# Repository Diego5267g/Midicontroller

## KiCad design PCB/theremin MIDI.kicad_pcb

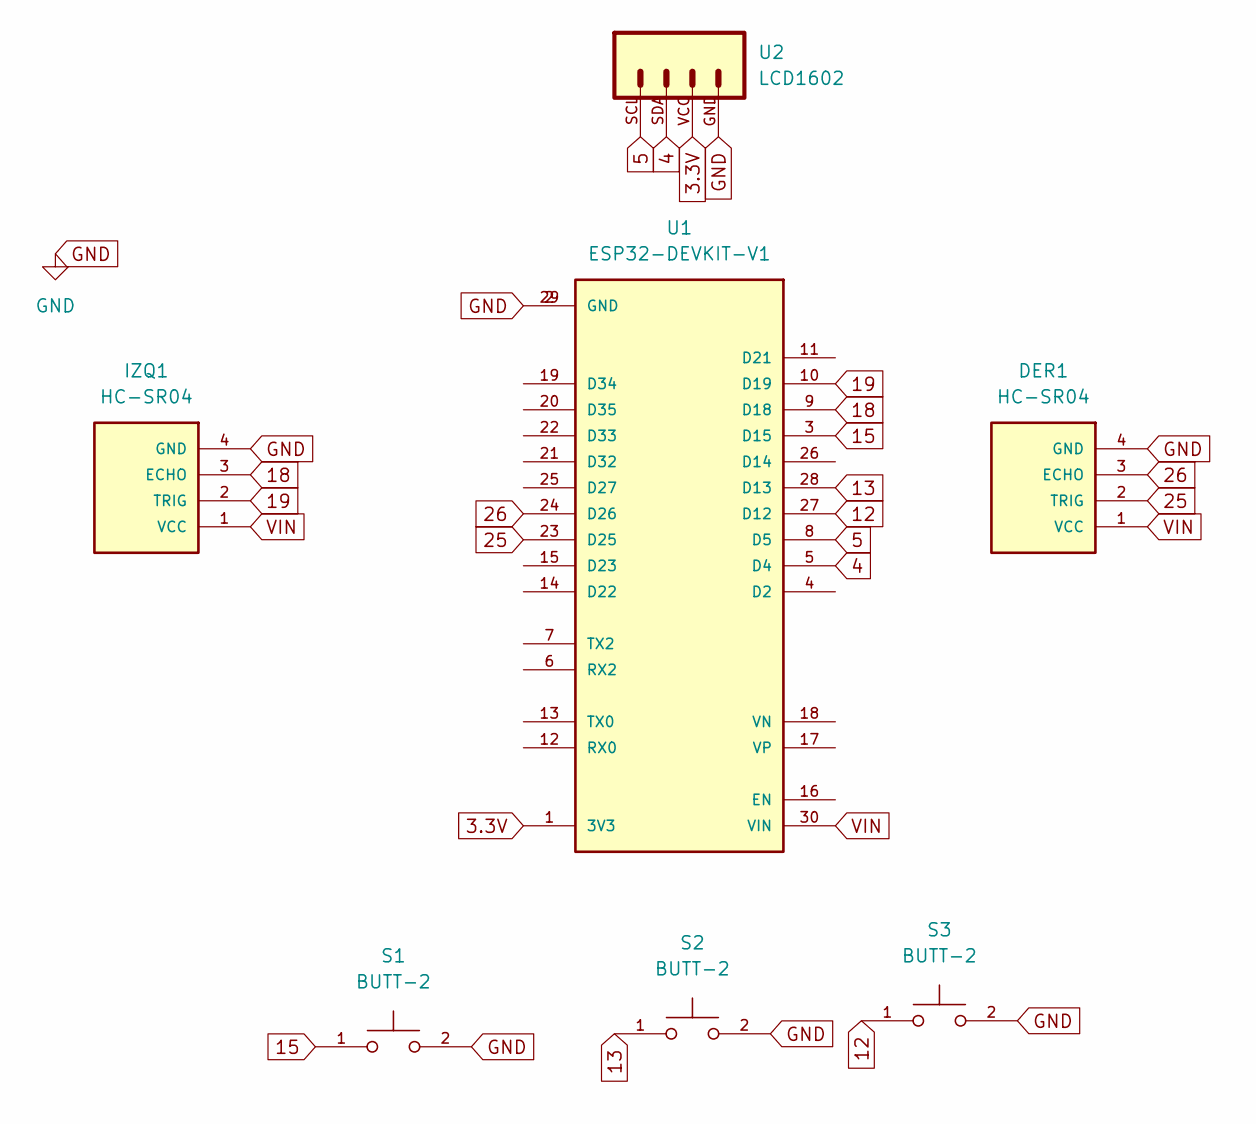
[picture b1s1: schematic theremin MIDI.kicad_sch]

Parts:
DER1: HC-SR04; XCVR_HC-SR04
IZQ1: HC-SR04; XCVR_HC-SR04
S1, S2, S3: BUTT-2; SW_BUTT-2; PARTREV N/A
U1: ESP32-DEVKIT-V1; MODULE_ESP32_DEVKIT_V1; PARTREV N/A
U2: LCD1602; LCD1602-PORT

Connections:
3.3V: U1.1 (3V3), U2.VCC
4: U1.5 (D4), U2.SDA
5: U1.8 (D5), U2.SCL
12: S3.1, U1.27 (D12)
13: S2.1, U1.28 (D13)
15: S1.1, U1.3 (D15)
18: IZQ1.3 (ECHO), U1.9 (D18)
19: IZQ1.2 (TRIG), U1.10 (D19)
25: DER1.2 (TRIG), U1.23 (D25)
26: DER1.3 (ECHO), U1.24 (D26)
GND: DER1.4 (GND), IZQ1.4 (GND), S1.2, S2.2, S3.2, U1.2 (GND), U1.29 (GND), U2.GND
VIN: DER1.1 (VCC), IZQ1.1 (VCC), U1.30 (VIN)

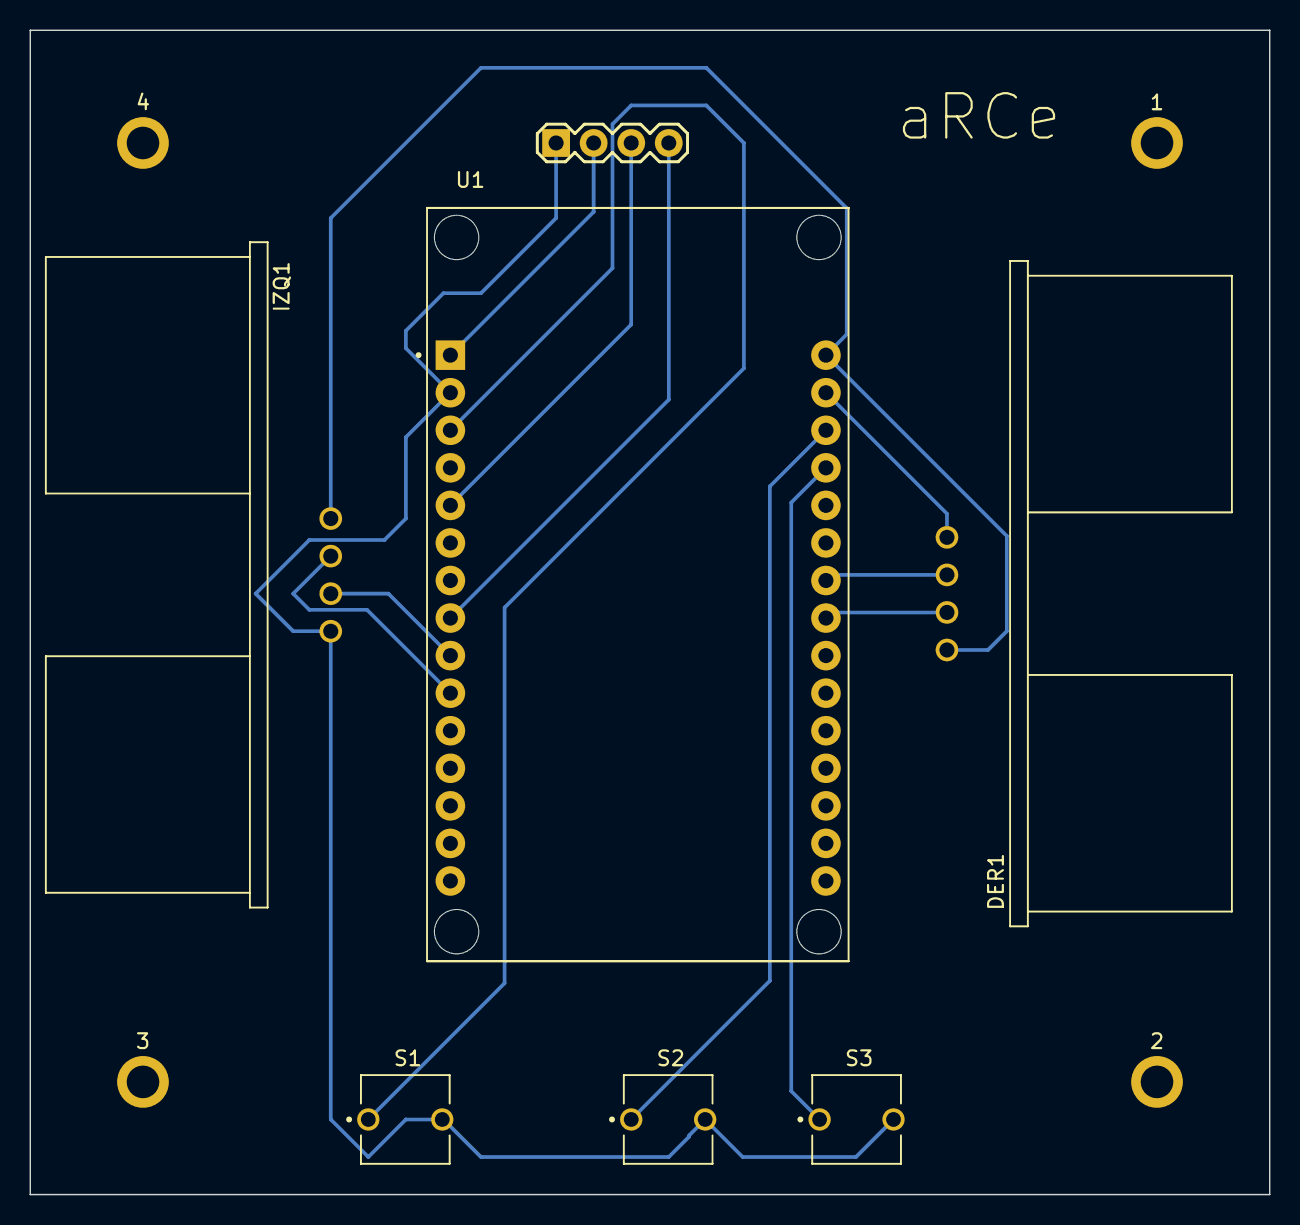
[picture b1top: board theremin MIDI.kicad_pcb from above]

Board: 2 copper layers, 83.8 x 78.7 mm, 11 parts (0 on the bottom side), 12 nets.

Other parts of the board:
1, 2, 3, 4: MountingHole_2.2mm_M2_ISO7380_Pad

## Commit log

2023-11-25 Agregue el poster
2023-11-27 Agregue el esquematico
2023-12-01 agregue los archivos fuente
2023-12-01 agregue el codigo
2023-12-01 subi los archivos fuente de la PCB
